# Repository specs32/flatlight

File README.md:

# flatlight

__What is Flatlight?__

A (relatively) powerful light, that nicely fits into your pockets because it's flat like a phone ;)

This Project is intended for educational and private use. (Probably to show how not to do a few things^^)

I designed the "Flatlight" myself, searching for circuits online, creating the schematics and layout with KiCAD.
I  built a few prototypes from bare copper PCB to the finished device, including printing the transparencys, exposing, developing, etching, cleaning, filing, placing the components and toasting the board on my old camping gas stove.

And as you can see im not much of a programmer ...

I got a lot of positive feedback from everyone, so I thought its time to share ! :)

__Building the Flatlight__

You should find everything you need in the KiCAD Folder to get started Hardwarewise.

__Code for the Flatlight__

It started out as a C++ Project in Eclipse, but i found that pretty difficult to set up and handle, so i switched to arduino.
The Arduino Programm is for the Flatlight . 

<B>The Software is Licensed under the GNU Public License 3.0, please include that in your Code</B>

<B> The Hardware is Licensed under CC-BY-SA 4.0 please include this on your Silkscreen or Top/Bottom Copper Layer</B>

Both Licenses can be found in the docs folder

Thanks to everyone who supported me  !!!

HAVE FUN !!!

-Nico

PS: Thanks and credits to cpldcpu for the nice tiny library which i forked here to adapt it to sk6812 RGBW LEDs!

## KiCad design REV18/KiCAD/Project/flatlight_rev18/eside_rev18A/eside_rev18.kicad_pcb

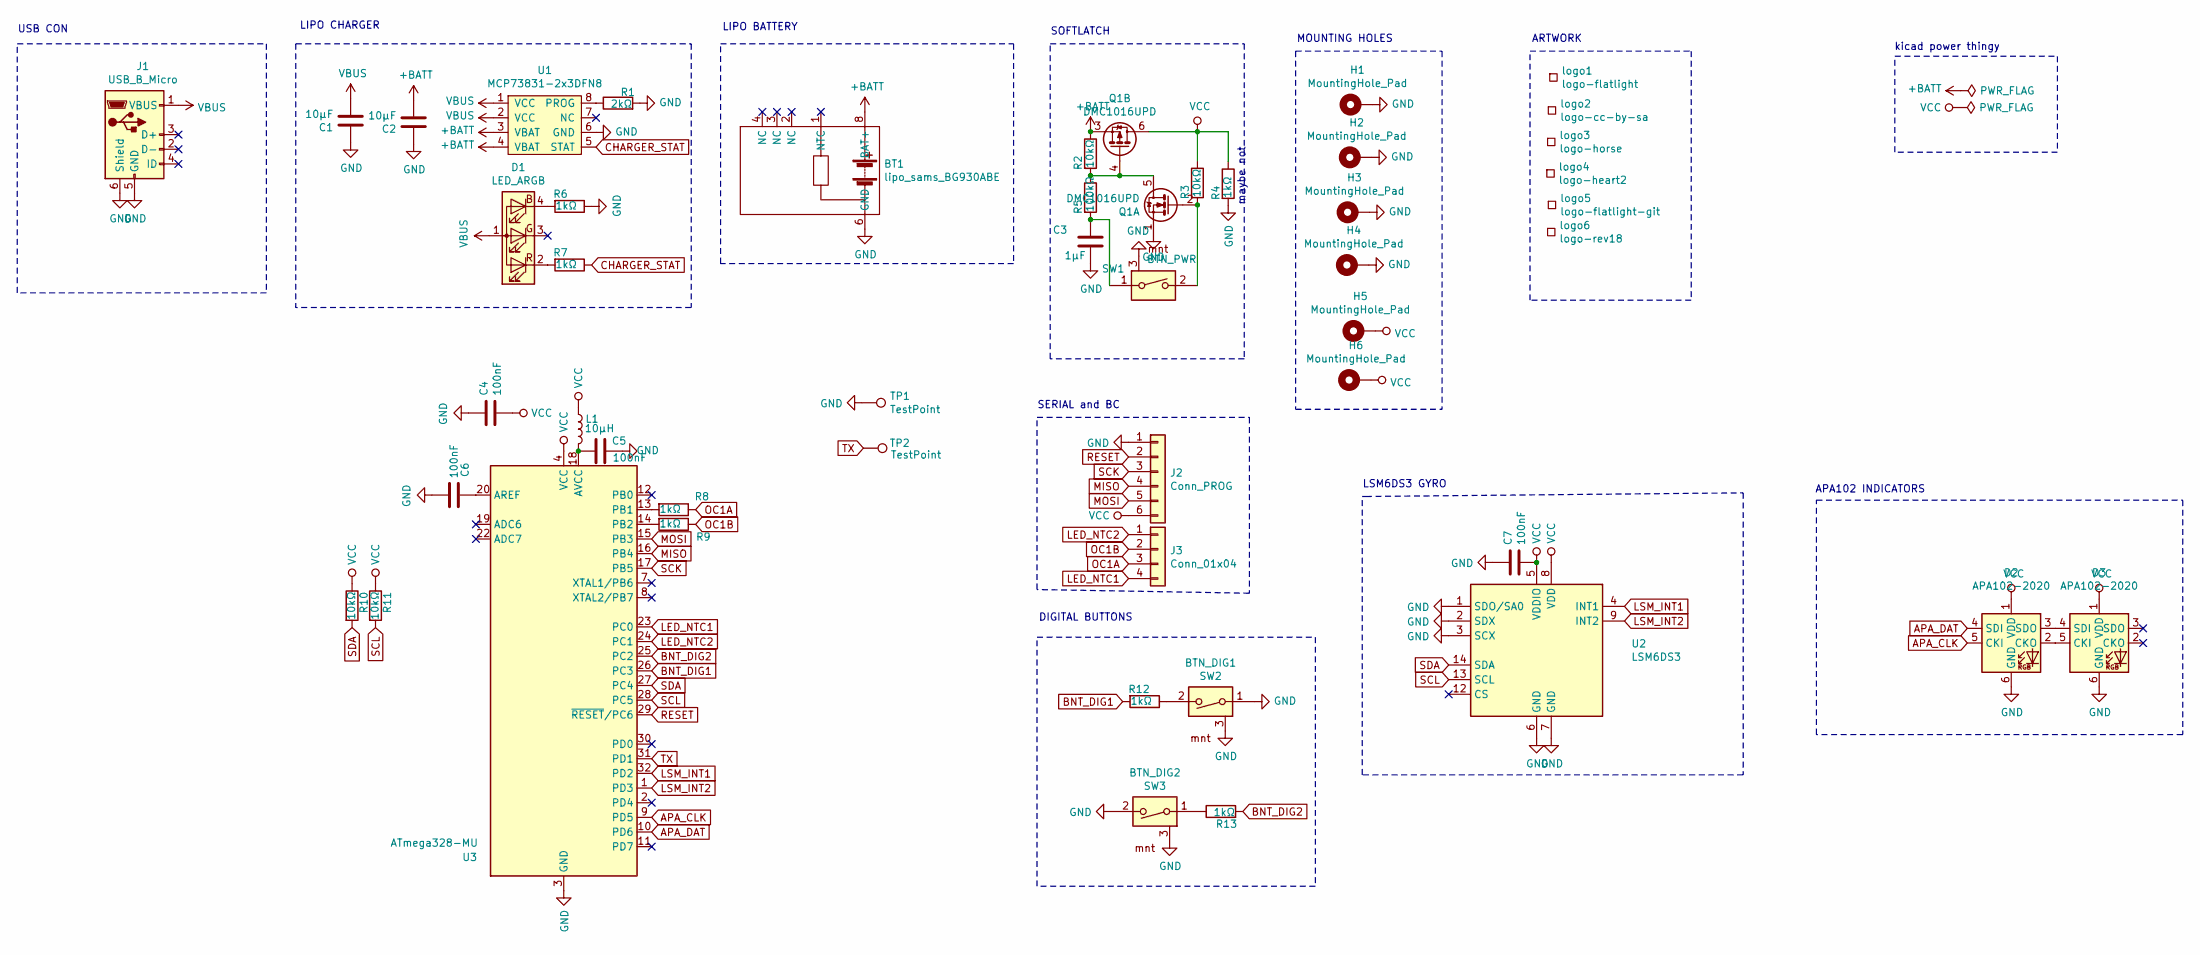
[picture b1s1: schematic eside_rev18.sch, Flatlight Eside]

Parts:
BT1: lipo_sams_BG930ABE; lipo_samsung_BG930ABE
C1: 10µF; C_0805_2012Metric
C2: 10µF; C_1206_3216Metric_Pad1.42x1.75mm_HandSolder
C3: 1µF; C_0805_2012Metric
C4, C5, C6, C7: 100nF; C_0603_1608Metric
D1: LED_ARGB; 0606_ARGB_LED
D2, D3: APA102-2020; LED-APA102-2020
H1, H2, H3, H4, H5, H6: MountingHole_Pad; MountingHole_2.2mm_M2_Pad_Via
J1: USB_B_Micro; USB_Micro-B_Wuerth_629105150521
J2: Conn_PROG; Conn_01x06_SMD_2mm
J3: Conn_01x04; PinHeader_1x04_P2.00mm_Vertical
L1: 10µH; L_0805_2012Metric
Q1: DMC1016UPD; PowerPAK_SO-8_Dual
R1: 2kΩ; R_0603_1608Metric
R2, R3, R10, R11: 10kΩ; R_0603_1608Metric
R4, R6, R7, R8, R9, R12, R13: 1kΩ; R_0603_1608Metric
R5: 100kΩ; R_0603_1608Metric
SW1: BTN_PWR; white_nano_smd_switch
SW2: BTN_DIG1; white_nano_smd_switch
SW3: BTN_DIG2; white_nano_smd_switch
TP1, TP2: TestPoint; TestPoint_Pad_1.0x1.0mm
U1: MCP73831-2x3DFN8; DFN-8-1EP_3x2mm_P0.5mm_EP1.75x1.45mm
U2: LSM6DS3; Bosch_LGA-14_3x2.5mm_P0.5mm
U3: ATmega328-MU; QFN-32-1EP_5x5mm_P0.5mm_EP3.1x3.1mm
logo1: logo-flatlight; logo_flatlight
logo2: logo-cc-by-sa; cc-by-sa
logo3: logo-horse; logo_horse
logo4: logo-heart2; logo_heart3
logo5: logo-flatlight-git; logo_flatlight_git_silk
logo6: logo-rev18; logo_REV18

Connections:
+BATT: BT1.7 (BAT+), BT1.8 (BAT+), C2.2, Q1.3 (1), R2.1, U1.3 (VBAT), U1.4 (VBAT)
APA_CLK: D2.5 (CKI), U3.9 (PD5)
APA_DAT: D2.4 (SDI), U3.10 (PD6)
BNT_DIG1: R12.2, U3.26 (PC3)
BNT_DIG2: R13.2, U3.25 (PC2)
CHARGER_STAT: R7.1, U1.5 (STAT)
GND: BT1.5 (GND), BT1.6 (GND), C1.1, C2.1, C3.2, C4.1, C5.1, C6.2, C7.1, D2.6 (GND), D3.6 (GND), H1.1, H2.1, H3.1, H4.1, J1.5 (GND), J1.6 (Shield), J2.1, Q1.1 (S), R1.2, R4.2, R6.1, SW1.3, SW2.1, SW2.3, SW3.2, SW3.3, TP1.1, U1.6 (GND), U1.9 (GND), U2.1 (SDO/SA0), U2.2 (SDX), U2.3 (SCX), U2.6 (GND), U2.7 (GND), U3.3 (GND), U3.5 (GND), U3.21 (GND), U3.33 (GND)
LED_NTC1: J3.4, U3.23 (PC0)
LED_NTC2: J3.1, U3.24 (PC1)
LSM_INT1: U2.4 (INT1), U3.32 (PD2)
LSM_INT2: U2.9 (INT2), U3.1 (PD3)
MISO: J2.4, U3.16 (PB4)
MOSI: J2.5, U3.15 (PB3)
unnamed: C3.1, R5.2, SW1.1
unnamed: C5.2, L1.2, U3.18 (AVCC)
unnamed: C6.1, U3.20 (AREF)
unnamed: D1.2 (RK), R7.2
unnamed: D1.4 (BK), R6.2
unnamed: D2.2 (CKO), D3.5 (CKI)
unnamed: D2.3 (SDO), D3.4 (SDI)
unnamed: Q1.2 (G), R3.2, SW1.2
unnamed: Q1.4 (G), Q1.5 (D), R2.2, R5.1
unnamed: R1.1, U1.8 (PROG)
unnamed: R8.2, U3.13 (PB1)
unnamed: R9.2, U3.14 (PB2)
unnamed: R12.1, SW2.2
unnamed: R13.1, SW3.1
OC1A: J3.3, R8.1
OC1B: J3.2, R9.1
RESET: J2.2, U3.29 (~RESET~/PC6)
SCK: J2.3, U3.17 (PB5)
SCL: R11.2, U2.13 (SCL), U3.28 (PC5)
SDA: R10.2, U2.14 (SDA), U3.27 (PC4)
TX: TP2.1, U3.31 (PD1)
VBUS: C1.2, D1.1 (A), J1.1 (VBUS), U1.1 (VCC), U1.2 (VCC)
VCC: C4.2, C7.2, D2.1 (VDD), D3.1 (VDD), H5.1, H6.1, J2.6, L1.1, Q1.6 (D), R3.1, R4.1, R10.1, R11.1, U2.5 (VDDIO), U2.8 (VDD), U3.4 (VCC), U3.6 (VCC)

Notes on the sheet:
APA102 INDICATORS
DIGITAL BUTTONS
MOUNTING HOLES
ARTWORK
LIPO BATTERY
LIPO CHARGER
USB CON
SERIAL and BC
SOFTLATCH
LSM6DS3 GYRO
kicad power thingy
maybe not

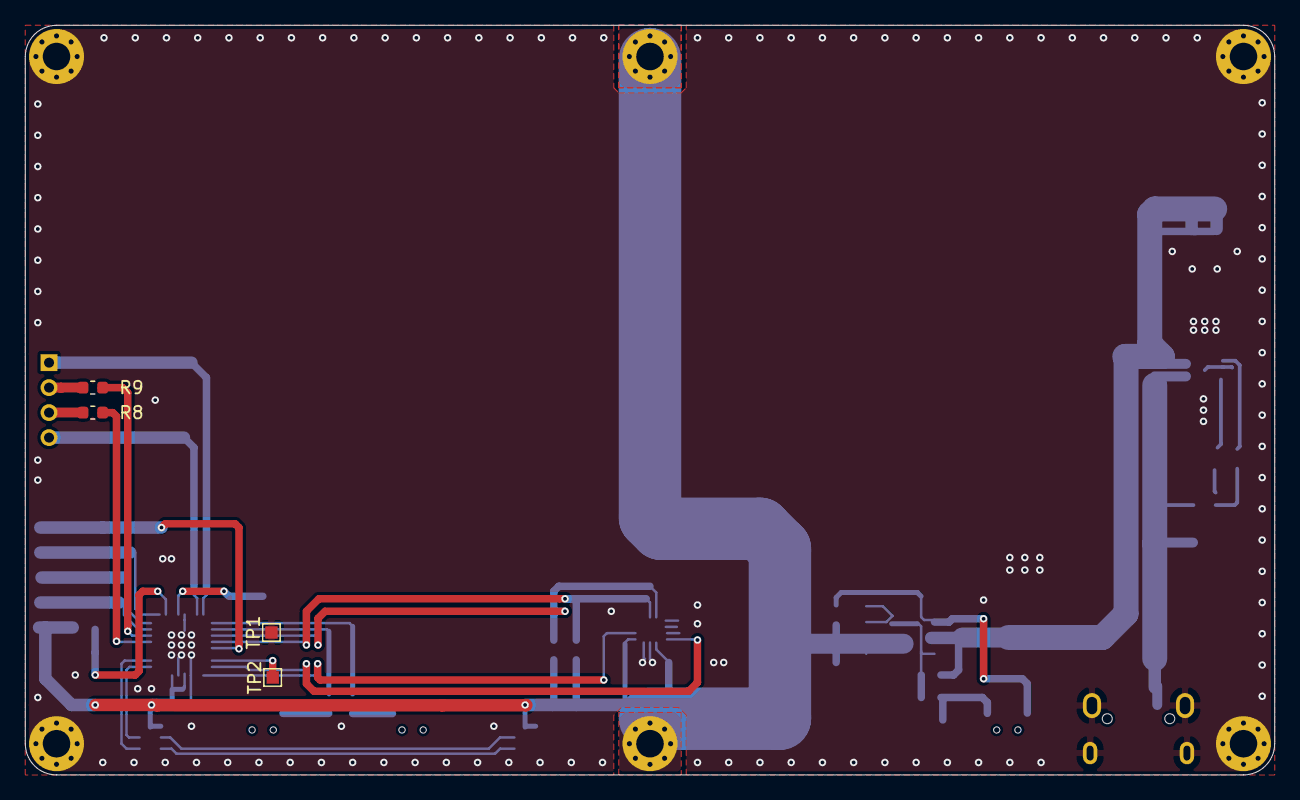
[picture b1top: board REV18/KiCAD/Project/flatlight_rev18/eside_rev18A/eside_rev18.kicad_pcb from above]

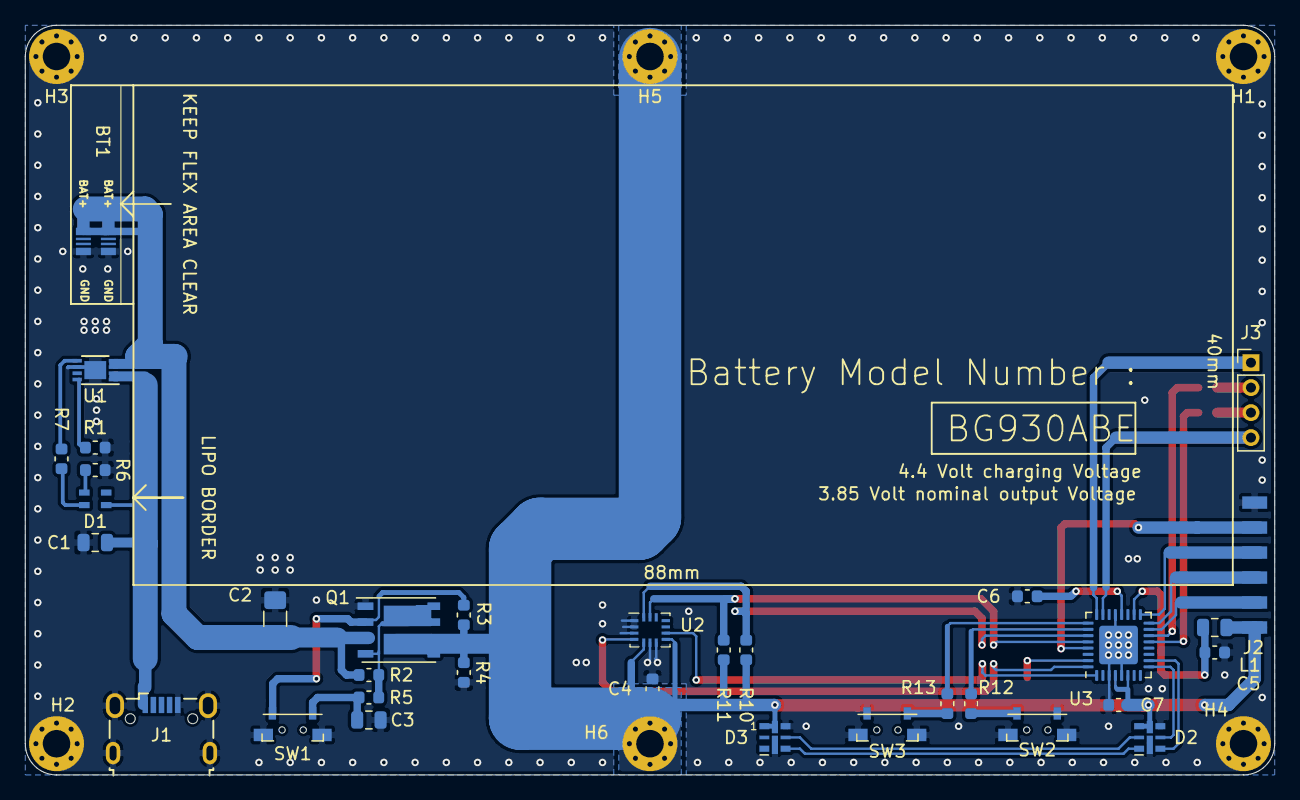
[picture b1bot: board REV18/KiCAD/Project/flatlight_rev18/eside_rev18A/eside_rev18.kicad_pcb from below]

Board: 2 copper layers, 100.0 x 60.0 mm, 49 parts (40 on the bottom side), 36 nets.

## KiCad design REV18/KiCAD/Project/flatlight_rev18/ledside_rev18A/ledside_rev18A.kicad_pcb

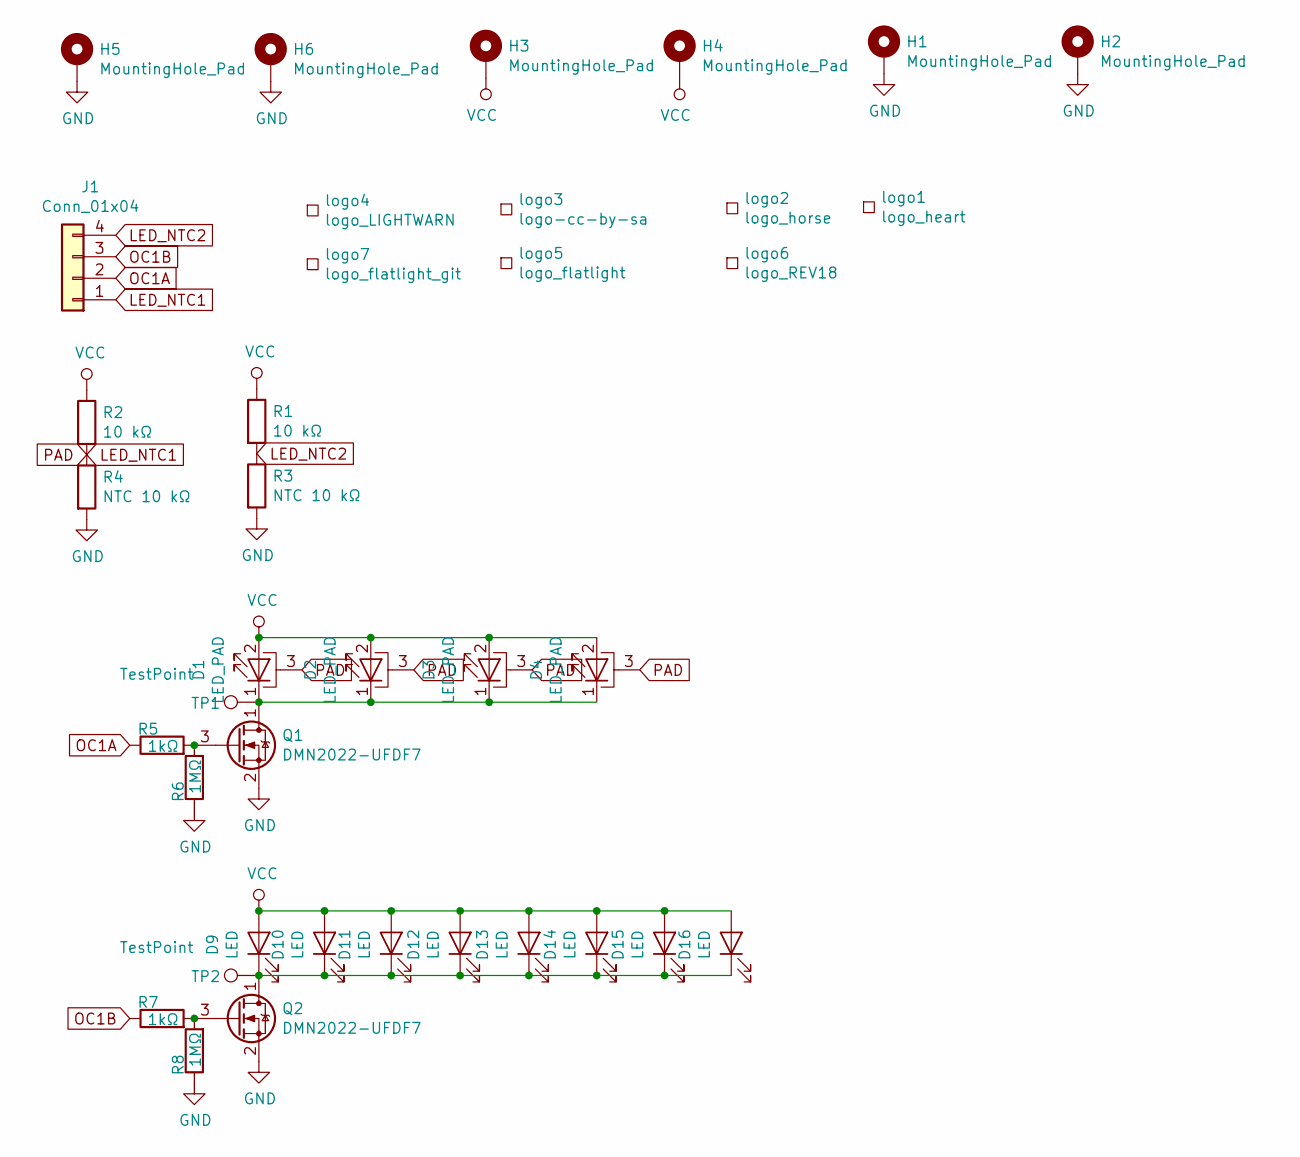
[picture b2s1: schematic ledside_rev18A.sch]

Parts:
D1, D2, D3, D4: LED_PAD; LED_Cree-XP-G
D9, D10, D11, D12, D13, D14, D15, D16: LED; LED_Cree-J-Series
H1, H2, H3, H4, H5, H6: MountingHole_Pad; MountingHole_2.2mm_M2_Pad_Via
J1: Conn_01x04; PinHeader_1x04_P2.00mm_Vertical
Q1, Q2: DMN2022-UFDF7; U-DFN2020-6 (Type F)
R1, R2: 10 kΩ; R_0603_1608Metric_Pad1.05x0.95mm_HandSolder
R3, R4: NTC 10 kΩ; R_0603_1608Metric_Pad1.05x0.95mm_HandSolder
R5, R7: 1kΩ; R_0603_1608Metric_Pad1.05x0.95mm_HandSolder
R6, R8: 1MΩ; R_0603_1608Metric_Pad1.05x0.95mm_HandSolder
TP1, TP2: TestPoint; TestPoint_Pad_1.5x1.5mm
logo1: logo_heart; logo_heart3
logo2: logo_horse
logo3: logo-cc-by-sa; cc-by-sa
logo4: logo_LIGHTWARN; logo_lightwarn_15mm
logo5: logo_flatlight
logo6: logo_REV18
logo7: logo_flatlight_git; logo_flatlight_git_silk

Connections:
GND: H1.1, H2.1, H5.1, H6.1, Q1.2 (S), Q2.2 (S), R3.2, R4.2, R6.1, R8.1
LED_NTC1: D1.3 (PAD), D2.3 (PAD), D3.3 (PAD), D4.3 (PAD), J1.1, R2.2, R4.1
LED_NTC2: J1.4, R1.2, R3.1
unnamed: D1.1 (K), D2.1 (K), D3.1 (K), D4.1 (K), Q1.1 (D), TP1.1
unnamed: D9.1 (K), D10.1 (K), D11.1 (K), D12.1 (K), D13.1 (K), D14.1 (K), D15.1 (K), D16.1 (K), Q2.1 (D), TP2.1
unnamed: Q1.3 (G), R5.2, R6.2
unnamed: Q2.3 (G), R7.2, R8.2
OC1A: J1.2, R5.1
OC1B: J1.3, R7.1
VCC: D1.2 (A), D2.2 (A), D3.2 (A), D4.2 (A), D9.2 (A), D10.2 (A), D11.2 (A), D12.2 (A), D13.2 (A), D14.2 (A), D15.2 (A), D16.2 (A), H3.1, H4.1, R1.1, R2.1

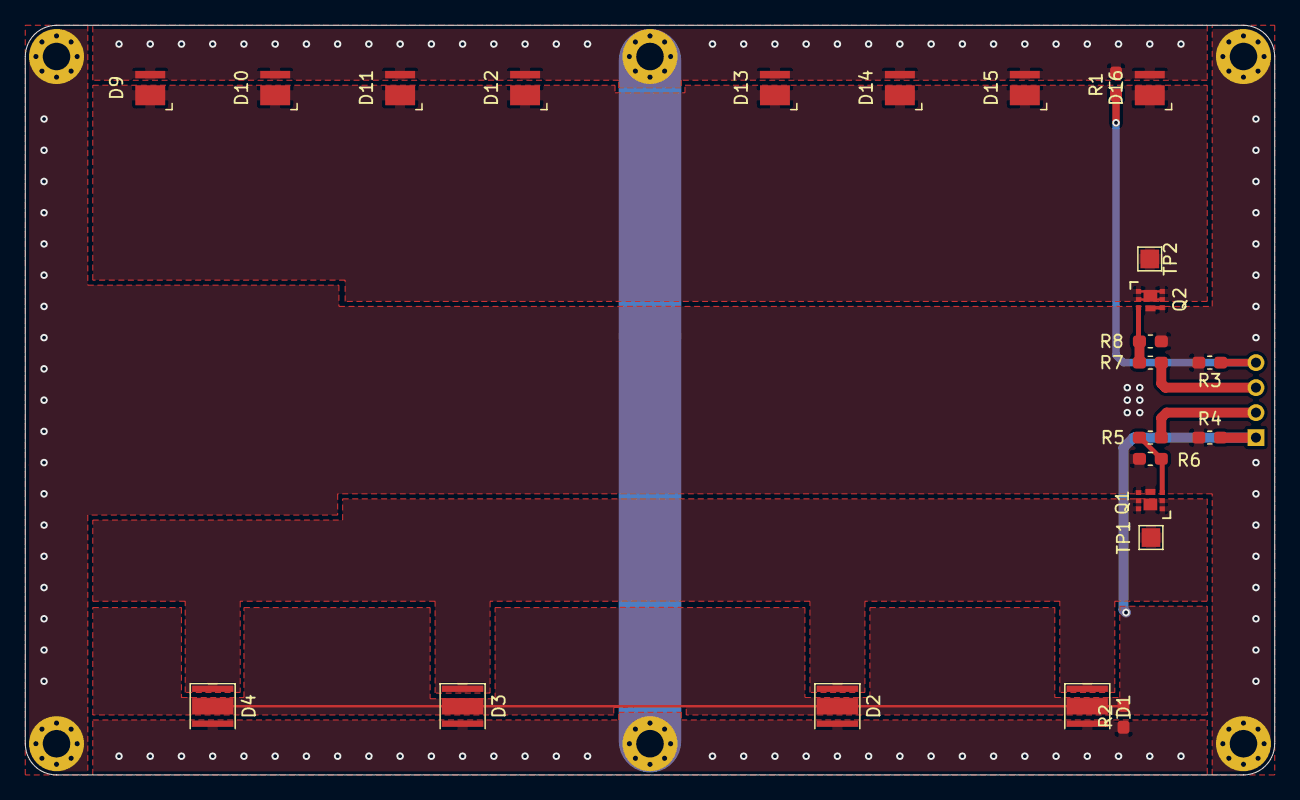
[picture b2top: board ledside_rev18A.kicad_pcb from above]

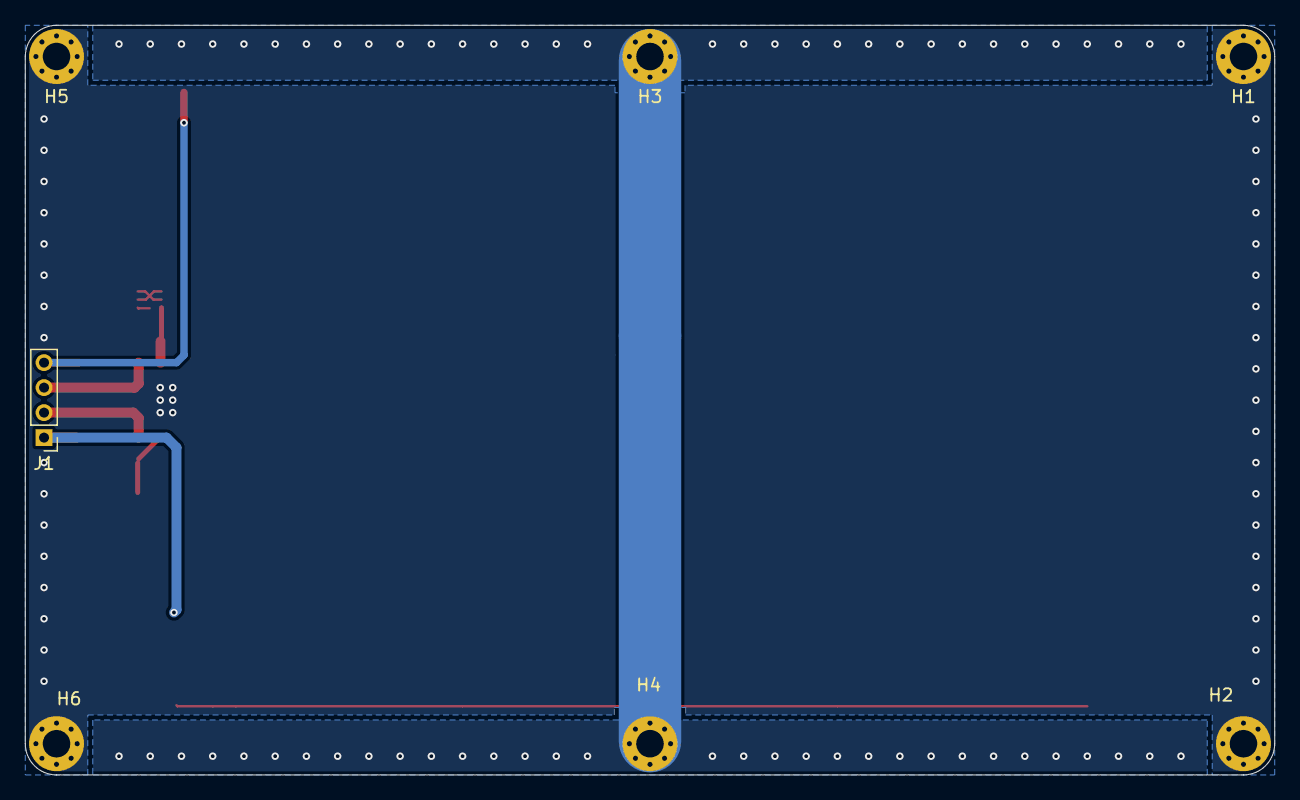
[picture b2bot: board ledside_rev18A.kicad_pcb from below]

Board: 2 copper layers, 100.0 x 60.0 mm, 38 parts (8 on the bottom side), 10 nets.

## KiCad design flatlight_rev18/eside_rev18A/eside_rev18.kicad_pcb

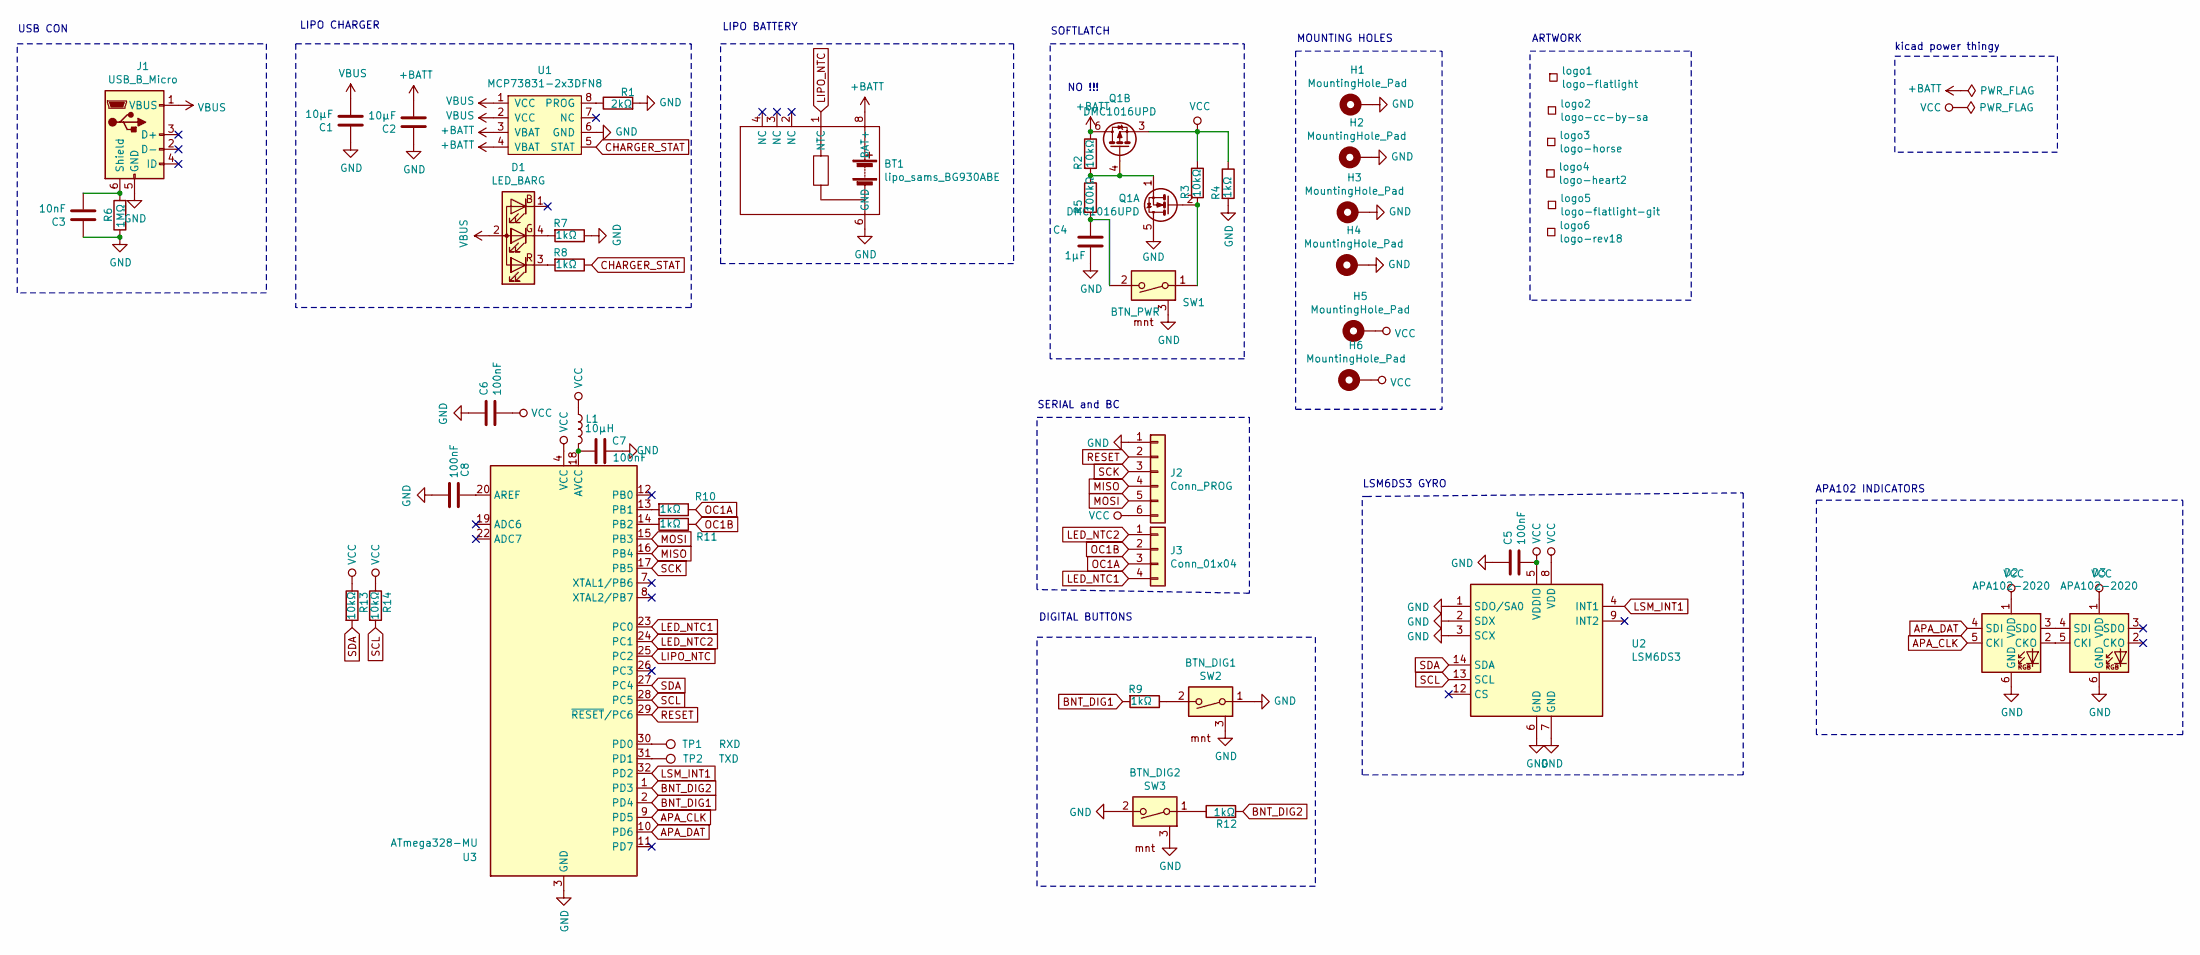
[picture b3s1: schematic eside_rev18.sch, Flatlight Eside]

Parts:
BT1: lipo_sams_BG930ABE; lipo_samsung_BG930ABE
C1: 10µF; C_0805_2012Metric
C2: 10µF; C_1206_3216Metric_Pad1.42x1.75mm_HandSolder
C3: 10nF; C_0805_2012Metric
C4: 1µF; C_0805_2012Metric
C5, C6, C7, C8: 100nF; C_0603_1608Metric
D1: LED_BARG; LED_BARG_1.4x1.5mm
D2, D3: APA102-2020; LED-APA102-2020
H1, H2, H3, H4, H5, H6: MountingHole_Pad; MountingHole_2.2mm_M2_Pad_Via
J1: USB_B_Micro; Conn_USBmicro-B_ebay-side_TH_GROUND
J2: Conn_PROG; Conn_01x06_SMD_2mm
J3: Conn_01x04; PinHeader_1x04_P2.00mm_Vertical
L1: 10µH; L_0805_2012Metric
Q1: DMC1016UPD; PowerPAK_SO-8_Dual
R1: 2kΩ; R_0603_1608Metric
R2, R3, R13, R14: 10kΩ; R_0603_1608Metric
R4, R7, R8, R9, R10, R11, R12: 1kΩ; R_0603_1608Metric
R5: 100kΩ; R_0603_1608Metric
R6: 1MΩ; R_0603_1608Metric
SW1: BTN_PWR; white_nano_smd_switch
SW2: BTN_DIG1; white_nano_smd_switch
SW3: BTN_DIG2; white_nano_smd_switch
TP1: RXD; TestPoint_Pad_D1.0mm
TP2: TXD; TestPoint_Pad_1.0x1.0mm
U1: MCP73831-2x3DFN8; DFN-8-1EP_2x3mm_P0.5mm_EP0.61x2.2mm
U2: LSM6DS3; Bosch_LGA-14_3x2.5mm_P0.5mm
U3: ATmega328-MU; QFN-32-1EP_5x5mm_P0.5mm_EP3.1x3.1mm
logo1: logo-flatlight; logo_flatlight
logo2: logo-cc-by-sa; cc-by-sa
logo3: logo-horse; logo_horse
logo4: logo-heart2; logo_heart2
logo5: logo-flatlight-git; logo_flatlight_git_silk
logo6: logo-rev18; logo_REV18

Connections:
+BATT: BT1.7 (BAT+), BT1.8 (BAT+), C2.2, Q1.6 (D), R2.1, U1.3 (VBAT), U1.4 (VBAT)
APA_CLK: D2.5 (CKI), U3.9 (PD5)
APA_DAT: D2.4 (SDI), U3.10 (PD6)
BNT_DIG1: R9.2, U3.2 (PD4)
BNT_DIG2: R12.2, U3.1 (PD3)
CHARGER_STAT: R8.1, U1.5 (STAT)
GND: BT1.5 (GND), BT1.6 (GND), C1.1, C2.1, C3.1, C4.2, C5.1, C6.1, C7.1, C8.2, D2.6 (GND), D3.6 (GND), H1.1, H2.1, H3.1, H4.1, J1.5 (GND), J2.1, Q1.5 (D), R1.2, R4.2, R6.1, R7.1, SW1.3, SW2.1, SW2.3, SW3.2, SW3.3, U1.6 (GND), U1.9 (GND), U2.1 (SDO/SA0), U2.2 (SDX), U2.3 (SCX), U2.6 (GND), U2.7 (GND), U3.3 (GND), U3.5 (GND), U3.21 (GND), U3.33 (GND)
LED_NTC1: J3.4, U3.23 (PC0)
LED_NTC2: J3.1, U3.24 (PC1)
LIPO_NTC: BT1.1 (NTC), U3.25 (PC2)
LSM_INT1: U2.4 (INT1), U3.32 (PD2)
MISO: J2.4, U3.16 (PB4)
MOSI: J2.5, U3.15 (PB3)
unnamed: C3.2, J1.6 (Shield), R6.2
unnamed: C4.1, R5.2, SW1.2
unnamed: C7.2, L1.2, U3.18 (AVCC)
unnamed: C8.1, U3.20 (AREF)
unnamed: D1.3 (RK), R8.2
unnamed: D1.4 (GK), R7.2
unnamed: D2.2 (CKO), D3.5 (CKI)
unnamed: D2.3 (SDO), D3.4 (SDI)
unnamed: Q1.1 (S), Q1.4 (G), R2.2, R5.1
unnamed: Q1.2 (G), R3.2, SW1.1
unnamed: R1.1, U1.8 (PROG)
unnamed: R9.1, SW2.2
unnamed: R10.2, U3.13 (PB1)
unnamed: R11.2, U3.14 (PB2)
unnamed: R12.1, SW3.1
unnamed: TP1.1, U3.30 (PD0)
unnamed: TP2.1, U3.31 (PD1)
OC1A: J3.3, R10.1
OC1B: J3.2, R11.1
RESET: J2.2, U3.29 (~RESET~/PC6)
SCK: J2.3, U3.17 (PB5)
SCL: R14.2, U2.13 (SCL), U3.28 (PC5)
SDA: R13.2, U2.14 (SDA), U3.27 (PC4)
VBUS: C1.2, D1.2 (A), J1.1 (VBUS), U1.1 (VCC), U1.2 (VCC)
VCC: C5.2, C6.2, D2.1 (VDD), D3.1 (VDD), H5.1, H6.1, J2.6, L1.1, Q1.3 (1), R3.1, R4.1, R13.1, R14.1, U2.5 (VDDIO), U2.8 (VDD), U3.4 (VCC), U3.6 (VCC)

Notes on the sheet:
APA102 INDICATORS
DIGITAL BUTTONS
MOUNTING HOLES
ARTWORK
LIPO BATTERY
LIPO CHARGER
USB CON
SERIAL and BC
SOFTLATCH
LSM6DS3 GYRO
NO !!!
kicad power thingy

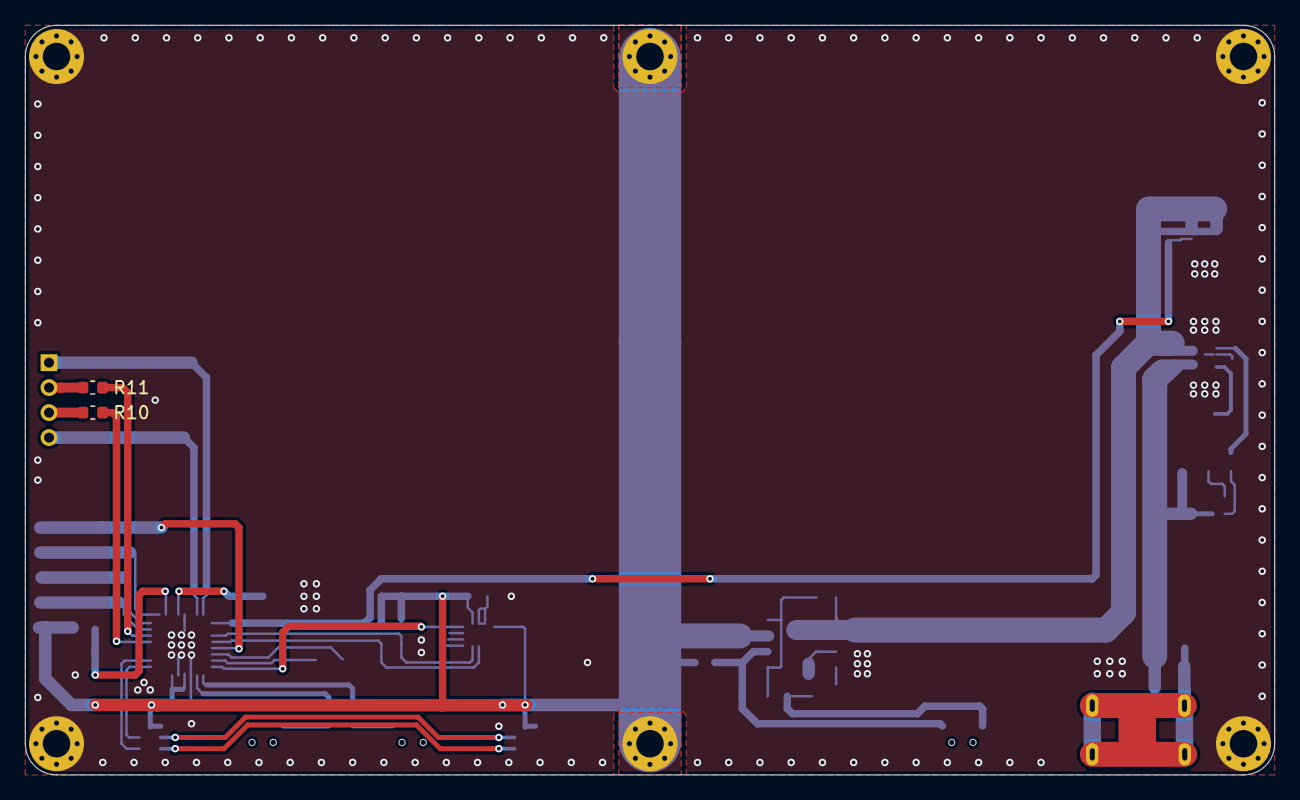
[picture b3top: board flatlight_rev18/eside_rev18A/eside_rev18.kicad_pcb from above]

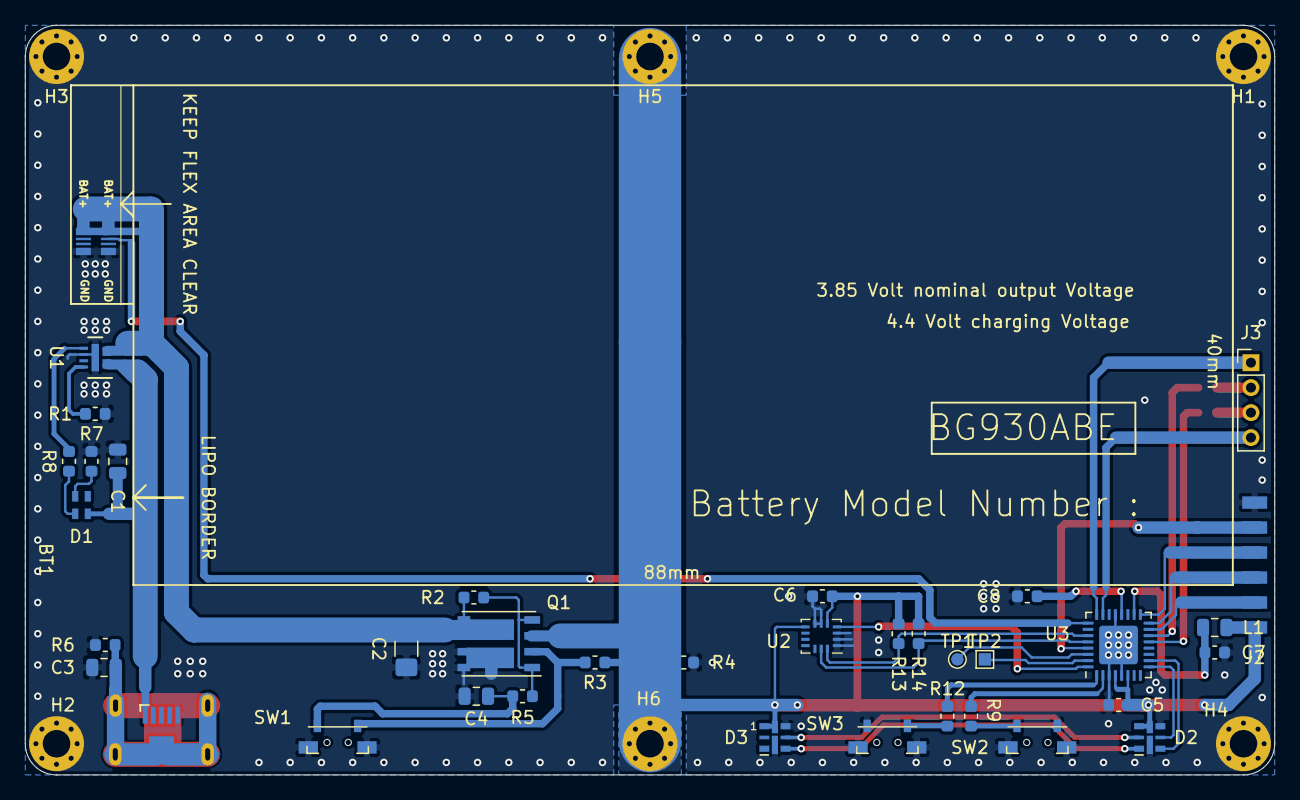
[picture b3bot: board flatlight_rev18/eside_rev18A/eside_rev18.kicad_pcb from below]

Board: 2 copper layers, 100.0 x 60.0 mm, 51 parts (43 on the bottom side), 38 nets.

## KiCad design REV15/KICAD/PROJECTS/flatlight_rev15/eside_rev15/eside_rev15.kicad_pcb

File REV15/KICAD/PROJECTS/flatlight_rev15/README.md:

/*

Flatlight Rev 15

 --- KiCad - Files

*/

NOTE : 

The gerber_rev15 folder contains updated PCB_NEW designs for kicad 
that are _not_ applied to the single PCB versions in the eside / ledside folders.

TODO : 

- need to update files single PCB files

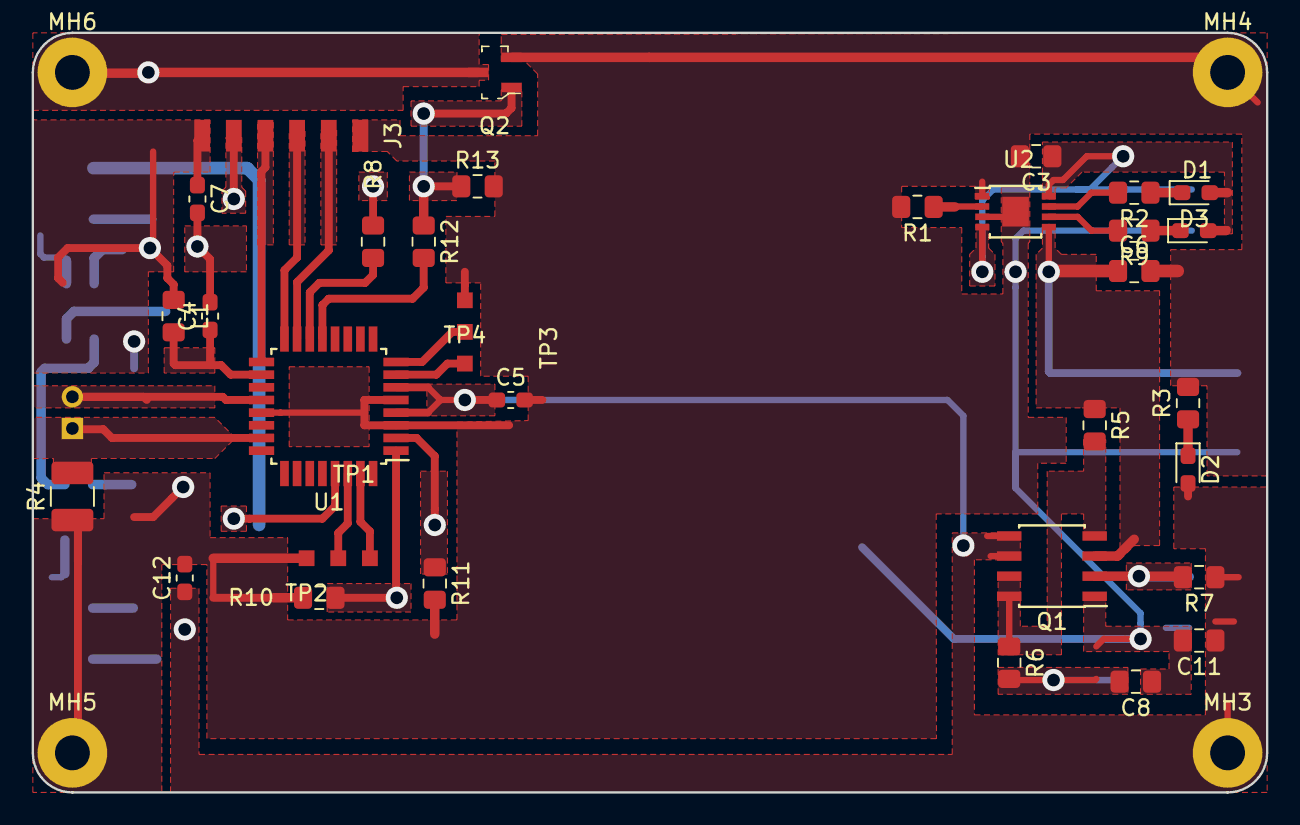
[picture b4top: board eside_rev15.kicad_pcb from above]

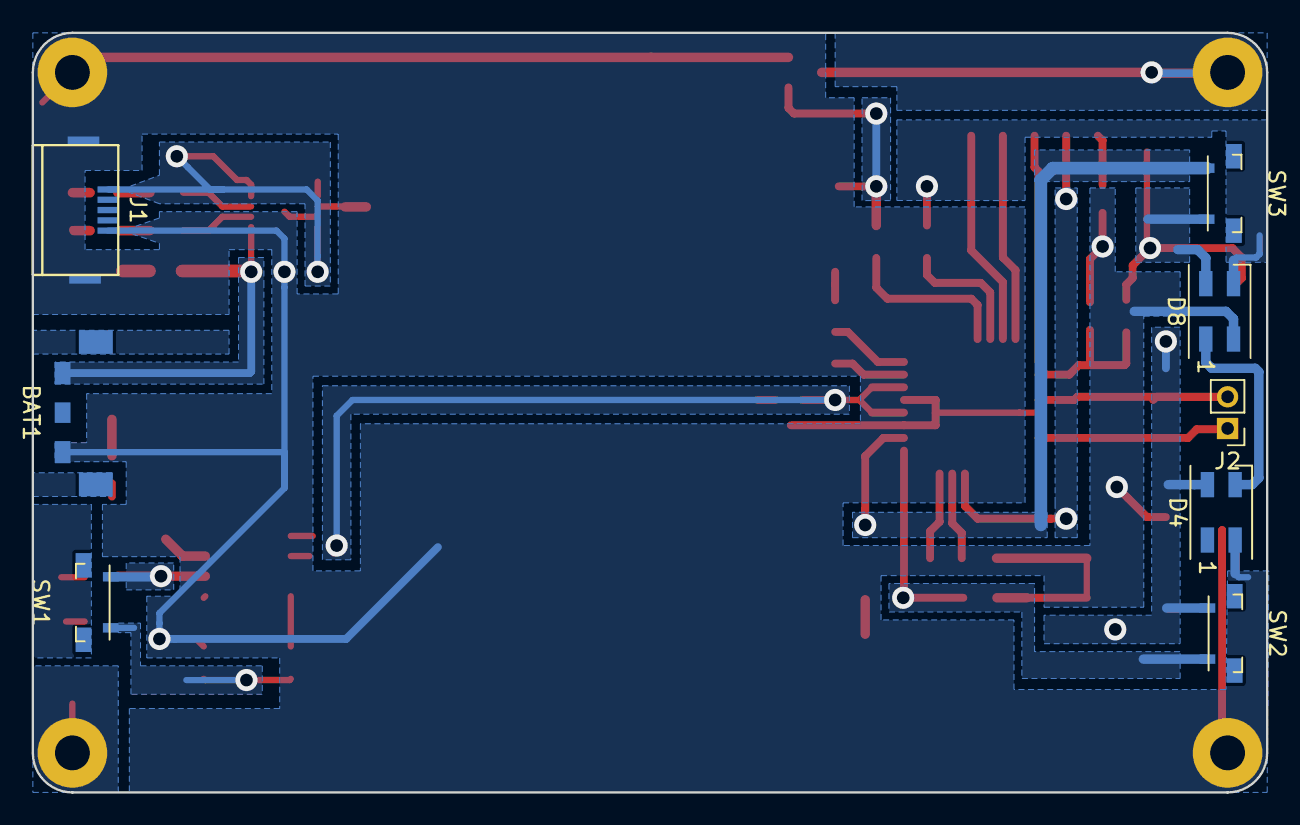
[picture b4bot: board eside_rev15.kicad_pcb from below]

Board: 2 copper layers, 78.0 x 48.0 mm, 46 parts (8 on the bottom side), 32 nets.

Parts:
BAT1: LIPO_W_NTC; CONN_AVX_RT_ANGLE_3pin_2.5mm_pitch
C3, C6, C11: 10µF; C_0805_2012Metric_Pad1.15x1.40mm_HandSolder
C4, C5, C7, C12: 100nF; C_0603_1608Metric_Pad1.05x0.95mm_HandSolder
C8: 1µF; C_0805_2012Metric_Pad1.15x1.40mm_HandSolder
D1: LED_RED; LED_0603_1608Metric_Pad1.05x0.95mm_HandSolder
D2: LED_PINK; LED_0603_1608Metric_Pad1.05x0.95mm_HandSolder
D3: LED_GREEN; LED_0603_1608Metric_Pad1.05x0.95mm_HandSolder
D4, D8: SK6812MINI; LED_SK6812MINI_PLCC4_3.5x3.5mm_P1.75mm
J1: USB_B_Micro; USB_Micro-B-CHINA
J2: TEMP_SENSOR; PinHeader_1x02_P2.00mm_Vertical
J3: ISP_CONN; Conn_01x06_SMD_2mm
L1: 10µH; L_0805_2012Metric_Pad1.15x1.40mm_HandSolder
MH3: VCC; MountingHole_2.2mm_M2_Pad
MH4, MH5: GND; MountingHole_2.2mm_M2_Pad
MH6: OC1A; MountingHole_2.2mm_M2_Pad
Q1: IRF7343PBF; SOIC-8_3.9x4.9mm_P1.27mm
Q2: IRLML6344TRPBF; SOT-23-3
R1: 1.2kΩ; R_0805_2012Metric_Pad1.15x1.40mm_HandSolder
R2, R3, R8, R9, R12: 1kΩ; R_0805_2012Metric_Pad1.15x1.40mm_HandSolder
R4: 15kΩ; R_1210_3225Metric_Pad1.42x2.65mm_HandSolder
R5, R7, R10, R11: 10kΩ; R_0805_2012Metric_Pad1.15x1.40mm_HandSolder
R6: 100kΩ; R_0805_2012Metric_Pad1.15x1.40mm_HandSolder
R13: 1MΩ; R_0805_2012Metric_Pad1.15x1.40mm_HandSolder
SW1: nano_sw; white_nano_smd_switch
SW2, SW3: SW_DIP_x01; white_nano_smd_switch
TP1: COM; 2_pad_smd_bat_conn
TP2, TP4: TestPoint; 1_pad_smd
TP3: OSC; 2_pad_smd_bat_conn
U1: ATmega88-20AU; TQFP-32_7x7mm_P0.8mm
U2: DIO5158; MSOP-8-1EP_3x3mm_P0.65mm_EP1.68x1.88mm

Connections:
+BATT: BAT1.1, C6.1, Q1.3, R5.1, U2.5
ADC0: J2.1, R4.2, U1.23
AREF: J2.2, U1.20
AVCC: C4.1, L1.2, U1.18
GND: BAT1.3, C3.2, C4.2, C5.2, C6.2, C7.2, C8.1, C11.2, C12.2, D4.2, D8.2, J1.5, J1.6, J3.1, MH4.1, MH5.1, Q1.1, Q2.2, R1.2, R3.2, R4.1, R10.2, R11.2, R13.2, TP2.1, TP4.1, U1.3, U1.5, U1.21, U2.1, U2.3, U2.9
MISO: J3.3, U1.16
MOSI: J3.2, U1.15
unnamed: C8.2, R6.2, SW1.1
unnamed: D1.1, R2.1
unnamed: D2.1, R3.1
unnamed: D3.1, R9.1
unnamed: D4.3, D8.1
unnamed: D8.3, R8.2
unnamed: MH6.1, Q2.3
unnamed: Q1.2, R7.2, SW1.2
unnamed: Q1.4, Q1.7, Q1.8, R5.2, R6.1
unnamed: Q2.1, R12.1, R13.1
unnamed: R1.1, U2.2
unnamed: R2.2, U2.7
unnamed: R9.2, U2.6
OC1A: R12.2, U1.13
OC1B: R8.1, U1.14
OSC_N: TP3.1, U1.7
OSC_P: TP3.2, U1.8
PD3: R10.1, SW2.2, U1.1
PD4: R11.1, SW3.1, U1.2
RESET: J3.5, U1.29
RX: TP1.2, U1.30
SCK: J3.4, U1.17
TX: TP1.1, U1.31
VBUS: C3.1, D1.2, D3.2, J1.1, U2.4, U2.8
VCC: C5.1, C7.1, C11.1, C12.1, D2.2, D4.4, D8.4, J3.6, L1.1, MH3.1, Q1.5, Q1.6, R7.1, SW2.1, SW3.2, U1.4, U1.6
